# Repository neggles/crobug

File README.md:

# crobug

### Render:

## y tho

cause you can't get suzyqable anymore

will add more details to this readme later

## Repository Structure
- `crobug` contains a suzy-q-alike adapter with a built in usb hub to give you both CCD and OTG gadget access at the same time
- `crobug-direct` foregoes the usb hub in service of being cheaper and easier to assemble, and also triggers BC1.2 mode for 1.5A charging
- `crobug-host` is the same as `crobug-direct` but with a host-mode micro-B connector for booting from a flash drive while using CCD
- `libraries/crobug.pretty` contains board-specific footprints
- `libraries/crobug.kicad_sym` contains board-specific symbols
- `libraries/shapes3D` contains board-specific STEP models (and a few extra)

## Building

### **building most likely does not work at the moment.** 
(I need to update kikit stuff to deal with KiCad 6 and also actually specify board dimensions, panel tabs etc still.)

Simply call `make` in the top-top level directory. The `build` directory will then contain:

- the main board and top board
- A panelized version of said boards
- zipped gerbers for the boards you can directly use for manufacturing

### Credit where it's due:

Makefile uses [Jan Mrázek](https://github.com/yaqwsx)'s [KiKit](https://github.com/yaqwsx/KiKit),
which I cannot recommend enough and will need to be available before running `make`

Jan's [jlcparts](https://yaqwsx.github.io/jlcparts/) app was also extremely useful in narrowing 
down part choices based on what JLCPCB have available.

### License
<br /><span xmlns:dct="http://purl.org/dc/terms/" property="dct:title">crobug</span> by
<a xmlns:cc="http://creativecommons.org/ns#" href="https://github.com/neggles" property="cc:attributionName" rel="cc:attributionURL">neggles</a>
is licensed under a
<a rel="license" href="http://creativecommons.org/licenses/by-sa/4.0/">
Creative Commons Attribution-ShareAlike 4.0 International License
</a>

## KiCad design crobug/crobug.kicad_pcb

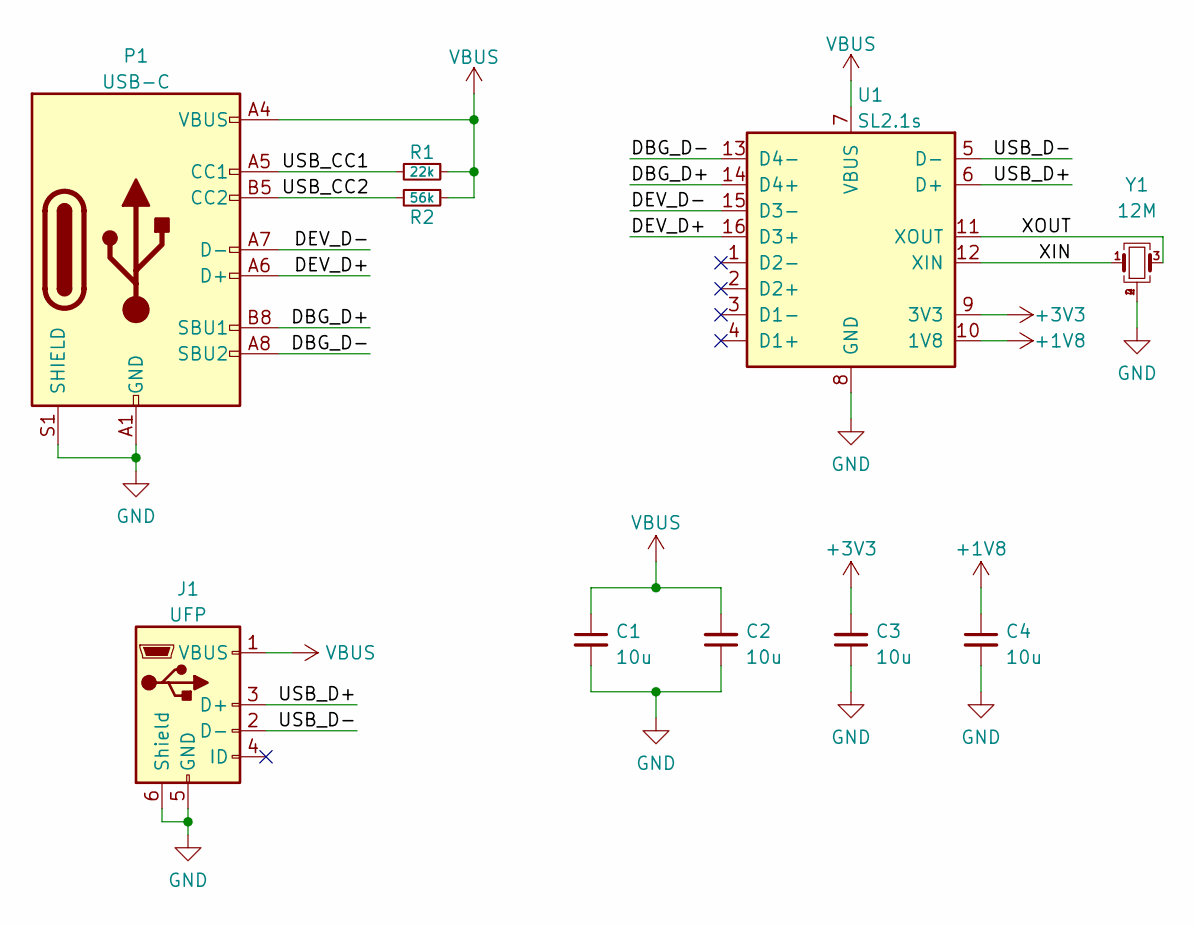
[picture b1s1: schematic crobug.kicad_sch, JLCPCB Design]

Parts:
C1, C2, C3, C4: 10u; C_0603_1608Metric
J1: UFP; Micro-USB_Xunpu-MU-109-ARY-C720609_AndVariants
P1: USB-C; USB_C_Plug_Xunpu_TYPEC-950-ARP24
R1: 22k; R_0603_1608Metric
R2: 56k; R_0603_1608Metric
U1: SL2.1s; SSOP-16_4.6x26.mm_P0.53mm; LCSC C2684433
Y1: 12M; Crystal_SMD_2520-4Pin_2.5x2.0mm; LCSC C9002

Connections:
+1V8: C4.1, U1.10 (1V8)
+3V3: C3.2, U1.9 (3V3)
/DBG_D+: P1.B8 (SBU1), U1.14 (D4+)
/DBG_D-: P1.A8 (SBU2), U1.13 (D4-)
/DEV_D+: P1.A6 (D+), U1.16 (D3+)
/DEV_D-: P1.A7 (D-), U1.15 (D3-)
/USB_CC1: P1.A5 (CC1), R1.2
/USB_CC2: P1.B5 (CC2), R2.2
/USB_D+: J1.3 (D+), U1.6 (D+)
/USB_D-: J1.2 (D-), U1.5 (D-)
/XIN: U1.12 (XIN), Y1.1
/XOUT: U1.11 (XOUT), Y1.3
GND: C1.2, C2.1, C3.1, C4.2, J1.5 (GND), J1.6 (Shield), P1.A1 (GND), P1.A12 (GND), P1.B1 (GND), P1.B12 (GND), P1.S1 (SHIELD), U1.8 (GND), Y1.2, Y1.4
VBUS: C1.1, C2.2, J1.1 (VBUS), P1.A4 (VBUS), P1.A9 (VBUS), P1.B4 (VBUS), P1.B9 (VBUS), R1.1, R2.1, U1.7 (VBUS)

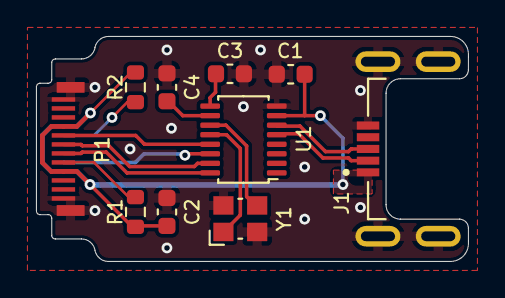
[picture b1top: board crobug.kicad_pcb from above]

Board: 2 copper layers, 24.0 x 12.5 mm, 10 parts (0 on the bottom side), 14 nets.

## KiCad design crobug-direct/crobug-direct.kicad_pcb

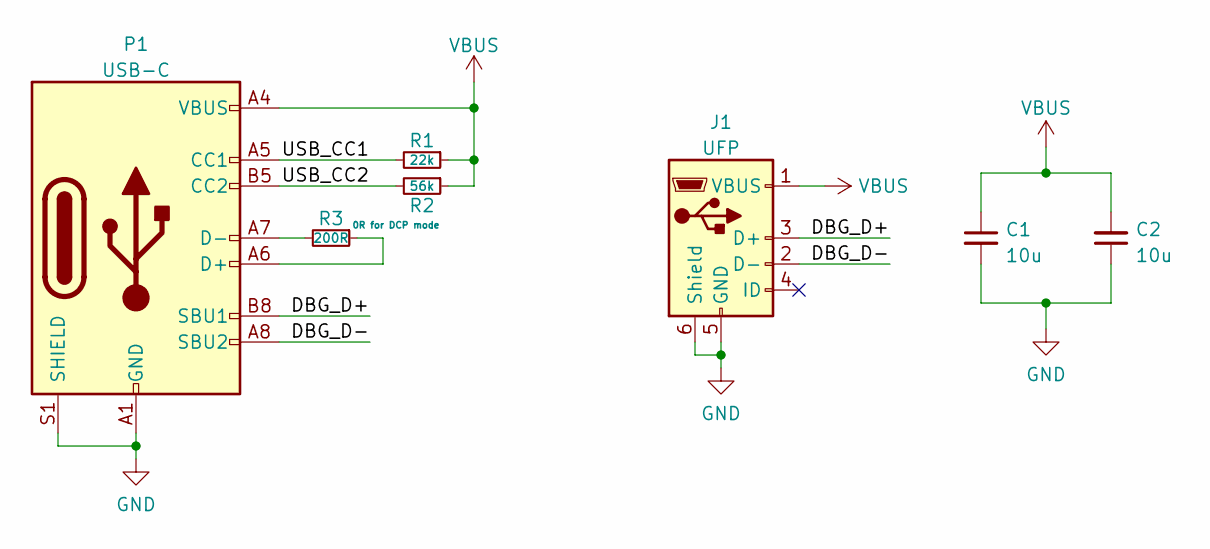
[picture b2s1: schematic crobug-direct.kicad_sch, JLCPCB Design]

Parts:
C1, C2: 10u; C_0603_1608Metric
J1: UFP; Micro-USB_Xunpu-MU-109-ARY-C720609_AndVariants
P1: USB-C; USB_C_Plug_Xunpu_TYPEC-950-ARP24
R1: 22k; R_0603_1608Metric
R2: 56k; R_0603_1608Metric
R3: 200R; R_0603_1608Metric

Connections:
/DBG_D+: J1.3 (D+), P1.B8 (SBU1)
/DBG_D-: J1.2 (D-), P1.A8 (SBU2)
/USB_CC1: P1.A5 (CC1), R1.2
/USB_CC2: P1.B5 (CC2), R2.2
GND: C1.2, C2.1, J1.5 (GND), J1.6 (Shield), P1.A1 (GND), P1.A12 (GND), P1.B1 (GND), P1.B12 (GND), P1.S1 (SHIELD)
unnamed: P1.A6 (D+), R3.1
unnamed: P1.A7 (D-), R3.2
VBUS: C1.1, C2.2, J1.1 (VBUS), P1.A4 (VBUS), P1.A9 (VBUS), P1.B4 (VBUS), P1.B9 (VBUS), R1.1, R2.1

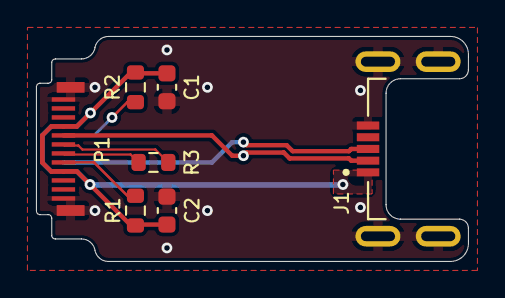
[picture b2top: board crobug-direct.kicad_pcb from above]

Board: 2 copper layers, 24.0 x 12.5 mm, 7 parts (0 on the bottom side), 8 nets.

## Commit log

2022-12-01 init
